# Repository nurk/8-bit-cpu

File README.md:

This repository contains my design of the Ben Eater 8-bit computer.  I call it an 8-CPU instead of a computer because to me it feels more like a CPU.

If you were to do a checkout of this, it is basically a KiCad project folder.  It will not contain all the symbols I used because the ones I designed I made global in KiCad, but I added a PDF of all the schematics.

You will also find my instruction set, the code to program the EEPROM's and the code to program the CPU which includes my test programs.

Below is a little badly written story of my journey.

## 8-bit CPU
I have always been intrigued by electronics by have never done anything with it.

A while back I found a video series by Ben Eater about building an 8-bit computer on breadboards ([YouTube](https://www.youtube.com/playlist?list=PLowKtXNTBypGqImE405J2565dvjafglHU)).  Watching the series I learned a lot about how CPU's (could) work and was really fascinated.  It all did not seem that complicated.

So after thinking about it for a while and checking my finances (It is not really cheap) I decided to build a variation of it.   But first I did some research and set some goals.

The research taught me that I should not skimp on breadboard quality.  There are a lot of people that write about this and the breadboards from BusBoard Prototype Systems seem to be one of the best.

Next I started digging into what types of 74 series logic chips there are.  I learned that the 74LS series that Ben uses are TTL logic chips but they are rather power hungry.  I decided I wanted to go with CMOS logic chips because they are more efficient.  In the end I went for 74HCT chips.  They are CMOS chips with TTL level support.  I went for this because I don't really know anything about this and I was not sure if I needed TTL level support in some parts.

So the chip series was decided and the breadboard brand was decided, now I needed a way to get all these things.  I started searching for those online and found the usual suspects: 
* Farnell
* Digikey
* Mouser
* ...

I live in Belgium so delivery costs, import taxes and VAT were important.  After a test order from [Mouser](https://www.mouser.be/) I learned that they take care of the VAT and the import taxes, and when you order over 50 EUR (excluding VAT) the delivery is free.  Just don't get caught at checkout because the prices on the site are without VAT.

I would also need a power supply.  I did not want to use a cut open USB cable but wanted some extra features.
* The device needed a global on/off switch
* I needed to be able to toggle the output on or off 
* Obviously the voltage should be settable
* The amperage should be limited
* I wanted over current protection so the output would be turned off if my creation would draw more than the set amps

On Amazon I found this [device](https://www.amazon.nl/dp/B0C1SMSW9F?ref=ppx_yo2ov_dt_b_product_details&th=1) that had all the features I wanted and it was not out of my budget.

Amazon was also used to buy the [wires](https://www.amazon.com.be/dp/B07V5FVSYL?psc=1&ref=ppx_yo2ov_dt_b_product_details) and initially some [resistors](https://www.amazon.com.be/dp/B0967TG6XR?ref=ppx_yo2ov_dt_b_product_details&th=1).  The wires were great and I ordered multiple of those because it seems this thing needs a lot of wire.  The resistors I hated and did not use.  The legs have a diameter of 0.3 mm which is just too thin.  When you want to insert them into a breadboard they just bend.  The resistors eventually also came from Mouser.

Next up, the goals of this build.
* I wanted a schematic of my build so I learned to use [KiCad](https://www.kicad.org/)
* Have more RAM so I could use all 8 address bits
* Have the RAM split so the first 128 bytes are for application memory and second 128 bytes are for data memory.  I did not want my application to overwrite itself
* Have an X register with +1 / -1 feature to enable specific loops and have it set the carry flag and zero flag
* Have a Stack
* Do not leave any input pins floating
* Have a 220 Ohm resistor on each LED (this includes each segment of the 7-segment display)
* Have a 100nF decoupling capacitor for each chip

The 220 Ohm resistor on each LED really made me think about component placement.  It dictated the layout on the breadboards.  Unlike what Ben does in his videos I could not just go from an output pin to ground.

After all the orders arrived I started building my CPU module by module in the order of the videos.  I would first design each module in KiCad and use my design to build it on breadboards.

While building I initially used 10k Ohm resistors to either pull-up or pull-down control signal pins.  That way I could use a jumper wire to switch its state without the pin being floating during the transition.  (The resistors were removed after wiring up the control signals.) The different modules were tested individually once they were finished.

When building the output module I noticed I did not order any 74HCT273 chips.  So I changed my design to use what I had which were 74HCT173 D-type flip flops.  In hindsight this seems to be a blessing in disguise because there seems to be a design issue with using the 74HCT273 as can be seen [here](https://www.youtube.com/playlist?list=PLyHdG0fm3K1j8sfvvdIarTFXVcFDdoBYp).

After finishing the clock, program counter, a register, alu, b register, output, ram and instruction register I decided to combine them and wire them up to the bus.  This is were I got hit with my first problem.

Whenever there were more than 4 LED's active in the RAM value and I would change the RAM output control signal (high to low or low to high) the RAM address register would reset.  I searched for hours what the cause could be but never figured it out.  I rewired stuff, replaced chips, disconnected modules from the bus, added pull-up and pull-down resisters, ... but everything stayed the same.  Motivation really sank so drastic measures needed to be taken.  Given the RAM address gets loaded by the program counter initially I decided I did not need a reset there and removed the reset line and tied the pins to ground.  *Problem solved*.

Next I built the last 4 modules: control logic, CPU flags, X register and stack.  When they were done I wired up everything.  Guess what, things did not work as expected.  Some of the problems I saw:
* The A register would reset randomly
* The X register would reset randomly
* The X register would load data from the bus at random points
* The X register would increment and decrement randomly
* The stack would increment and decrement randomly
* RAM not always writing

Those dreaded random resets were spreading.  Given I have no oscilloscope I could not really see what was going on with reset line but after some mental gymnastics I figured there must be some noise getting to the reset line.  Given I know nothing about electronics I started trying things.  

When I put a 10nF capacitor on the reset line close to the reset pin and ground of the A register it no longer did the random reset but the button to reset everything still worked.  I did the same with the X register and wired up the reset for the RAM address again with a 10nF capacitor.  No more random resets.  I still don't know why this is happening but it is fixed.  *Problem solved*.

Next up were the random actions in the X register and stack.  After searching the internet I found out that when you change the address on an EEPROM there is a period of time where the data is invalid (this is also in the datasheet).  This shows itself by data pins going high or low randomly during the invalid period.  This was triggering the random actions.

The first fix was not to trigger the load of the X register by just using an inverted control signal.  I used the non inverted control signal and the clock through a NAND gate to trigger the load.  This way the loading is tied to a clock transition which is in line with the rest of the design.  This made things better but did not solve everything.

After some more searching on the internet I found a post where someone explained that the entire computer reacts to the rising edge of the clock.  This includes the instruction register and the CPU flags which trigger address changes.  If you were to change the address on the falling edge of the clock the 'blips' on the EEPROM output would not matter.

I first thought about using the inverted clock for the instruction register and the CPU flags but decided against it.  I was not sure if this would have side effects.  Given I had some room below the instruction register I decided to add two more 74HCT173 D-type flip flops to latch the instruction register and the CPU flags on the falling edge of each clock.  These latched values are used as the address lines for the EEPROM's.  This solved all the problems of random actions occurring.

Lastly there was the problem of the RAM not always writing.  I was aware of issues with the RC circuit Ben has in his original design on the clock for the RAM input.  I already put in a diode to prevent back feeding any voltage as the capacitor discharges but I was still suspicious.  Given writing ram works with a push button in programming mode, which does not have an RC circuit on it, I figured it might work without.  After removing the RC circuit and just passing in the clock everything worked.

I now have an 8-bit breadboard CPU which supports addition, subtraction, push, pop, subroutines, ...

#### Some random bits:

I can program the CPU using the dip switches but that got old really quickly.  I wrote a little Arduino application that could program the CPU.  I just hook up the ground, the address lines, the data lines and write signal to the breadboard from an [Arduino Nano Every](https://store.arduino.cc/products/arduino-nano-every).  This saves a lot of time and does not discourage me from making changes and retesting.

On the internet there are many posts that say you have to add a lot of bulk capacitors to the breadboards in order to make it stable.  My CPU does not seem to need it.  It could be the quality of the breadboards, the fact that I used 74HCT chips or the quality of the power supply.  When running my Fibonacci program it draws a maximum of 350 mA.

I used an alternative to the EEPROM programmer designed by Ben.  Given I used an Arduino Nano Every, which has more digital pins, I did not have to combine the write signal into the shift registers.  I did have to rewire it because my EEPROM's did not seems to have the content I expected.

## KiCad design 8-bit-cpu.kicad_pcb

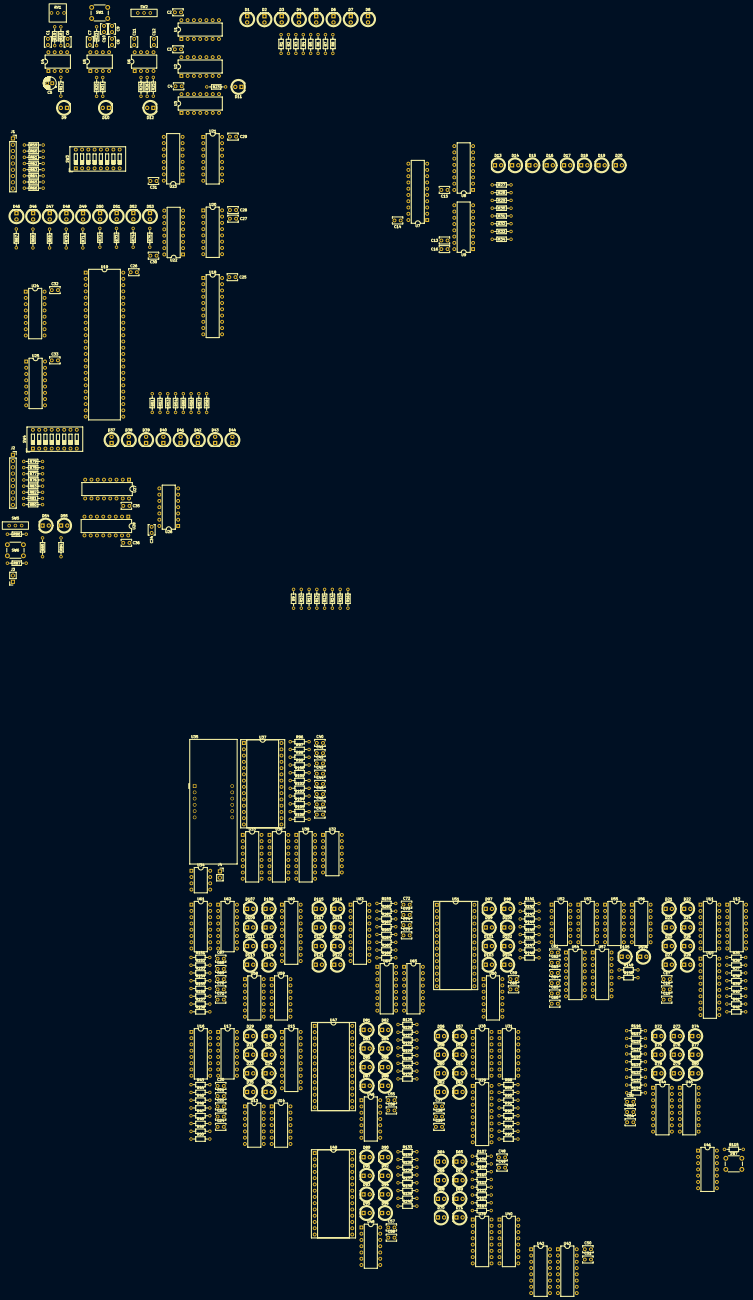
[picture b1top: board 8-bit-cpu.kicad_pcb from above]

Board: 2 copper layers, 440 parts (0 on the bottom side), 402 nets, no tracks yet.

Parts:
C1, C2, C3, C4, C7, C9, C10, C11, C14, C15, C16, C17, C18, C19, C20, C21, C22, C23, C24, C25, C26, C28, C29, C30, C31, C32, C33, C34, C35, C36, C37, C38, C39, C40, C41, C42, C45, C46, C47, C48, C49, C50, C51, C52, C53, C54, C55, C56, C57, C58, C59, C60, C61, C62, C63, C64, C65, C66, C67, C68, C69, C70, C71, C73, C74, C75: 100n; C_Disc_D4.0mm_W2.6mm_P2.50mm
C5: 1u; CP_Radial_D5.0mm_P2.00mm
C6, C8, C12, C13, C27, C43, C44, C72: 10n; C_Disc_D4.0mm_W2.6mm_P2.50mm
D1, D2, D3, D4, D5, D6, D7, D8, D13, D14, D15, D16, D17, D18, D19, D20, D21, D22, D23, D24, D25, D26, D27, D28, D29, D30, D31, D32, D33, D34, D35, D36, D37, D38, D39, D40, D41, D42, D43, D44, D55, D72, D73, D74, D107, D108, D109, D110, D111, D112, D113, D114: RED; LED_D5.0mm
D9, D10, D12, D45, D46, D47, D48, D49, D50, D51, D52, D53, D64, D65, D66, D67, D68, D69, D70, D71, D115, D116, D117, D118, D119, D120, D121, D122: YELLOW; LED_D5.0mm
D11, D81, D82, D83, D84, D85, D86, D87, D88, D89, D90, D91, D92, D93, D94, D95, D96, D97, D98, D99, D100, D101, D102, D103, D104: BLUE; LED_D5.0mm
D54, D56, D57, D58, D59, D60, D61, D62, D63, D75, D76, D77, D78, D79, D80, D105, D106: GREEN; LED_D5.0mm
J1: Arduino_Address_Programming_Header; PinSocket_1x09_P2.54mm_Vertical
J2: Arduino_Data_Programming_Header; PinSocket_1x09_P2.54mm_Vertical
J3: Arduino_Programming_Trigger_Header; PinSocket_1x02_P2.54mm_Vertical
J4: 2_Complement_Header; PinSocket_1x02_P2.54mm_Vertical
R1, R2, R3, R4, R5, R6, R7, R8, R17, R21, R23, R26, R27, R28, R29, R30, R31, R32, R33, R34, R35, R36, R37, R38, R39, R40, R41, R42, R43, R44, R45, R46, R47, R48, R49, R50, R51, R52, R53, R54, R55, R56, R57, R58, R67, R68, R69, R70, R71, R72, R73, R74, R75, R84, R85, R88, R89, R90, R91, R92, R93, R94, R95, R98, R99, R100, R101, R102, R103, R104, R105, R107, R108, R109, R110, R111, R112, R113, R114, R116, R117, R118, R119, R120, R121, R122, R123, R124, R125, R126, R127, R128, R129, R130, R131, R132, R133, R134, R135, R136, R137, R138, R139, R140, R141, R142, R143, R144, R145, R146, R147, R148, R149, R150, R151, R152, R153, R154, R155, R156, R157, R158, R159, R160, R161, R162, R163, R164, R165, R166: 220R; R_Axial_DIN0204_L3.6mm_D1.6mm_P7.62mm_Horizontal
R9, R10, R11, R12, R13, R14, R15, R16, R20, R24, R25, R59, R60, R61, R62, R63, R64, R65, R66, R76, R77, R78, R79, R80, R81, R82, R83, R86, R87, R106, R115: 10k; R_Axial_DIN0204_L3.6mm_D1.6mm_P7.62mm_Horizontal
R18, R19, R96: 1k; R_Axial_DIN0204_L3.6mm_D1.6mm_P7.62mm_Horizontal
R22: 1m; R_Axial_DIN0204_L3.6mm_D1.6mm_P7.62mm_Horizontal
R97: 100k; R_Axial_DIN0204_L3.6mm_D1.6mm_P7.62mm_Horizontal
RV1: 1m; Potentiometer_Bourns_3362U_Vertical
SW1, SW6, SW7: Button; SW_PUSH_6mm
SW2: Switch; Mini_Slide_Switch_CUI_THT_123
SW3, SW4: SW_DIP_x08; SW_DIP_SPSTx08_Slide_9.78x22.5mm_W7.62mm_P2.54mm
SW5: Programming Switch; Mini_Slide_Switch_CUI_THT_123
U1, U53, U55: 74HCT08; DIP-14_W7.62mm
U2, U46, U48, U50: 74HCT04; DIP-14_W7.62mm
U3: 74HCT32; DIP-14_W7.62mm
U4, U5, U6, U34: LMC555xN; DIP-8_W7.62mm
U7, U10, U15, U18, U29, U60, U63: 74HCT245; DIP-20_W7.62mm
U8, U9, U11, U12, U20, U21, U36, U38, U39, U40, U42, U43, U57: 74HCT173; DIP-16_W7.62mm
U13, U14: 74HCT86; DIP-14_W7.62mm
U16, U17: 74HCT283; DIP-16_W7.62mm
U19: 7130; DIP-48_W15.24mm
U22, U23, U24, U25, U27, U28, U54: 74HCT157; DIP-16_W7.62mm
U26, U41, U58, U59: 74HCT00; DIP-14_W7.62mm
U30, U31, U45: 74HCT161; DIP-16_W7.62mm
U32: 74HCT107; DIP-14_W7.62mm
U33: 74HCT139; DIP-16_W7.62mm
U35: LTC-5723HR; CA56-12SURKWA
U37, U47, U49, U51: AT28C64B; DIP-28_W15.24mm_Socket
U44: 74HCT138; DIP-16_W7.62mm
U52, U56: 74HCT02; DIP-14_W7.62mm
U61, U62, U64, U65: 74HCT193; DIP-16_W7.62mm

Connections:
+5V: C1.1, C2.1, C3.1, C4.1, C7.1, C11.1, C14.1, C15.1, C16.1, C17.1, C18.1, C19.1, C20.1, C21.1, C22.1, C23.1, C24.1, C25.1, C26.1, C28.1, C29.1, C30.1, C31.1, C32.1, C33.1, C34.1, C35.1, C36.1, C37.1, C38.1, C39.1, C42.1, C45.1, C46.1, C47.1, C48.1, C49.1, C50.1, C51.1, C52.1, C53.1, C54.1, C55.1, C56.1, C57.1, C58.1, C59.1, C60.1, C61.1, C62.1, C63.1, C64.1, C65.1, C66.1, C67.1, C68.1, C69.1, C70.1, C71.1, C73.1, C74.1, C75.1, J4.1, R18.1, R20.1, R22.1, R24.1, R25.1, R96.1, SW3.9, SW3.10, SW3.11, SW3.12, SW3.13, SW3.14, SW3.15, SW3.16, SW4.1, SW4.2, SW4.3, SW4.4, SW4.5, SW4.6, SW4.7, SW4.8, SW5.2 (B), SW6.1, SW7.1, U1.14 (VCC), U2.14 (VCC), U3.14 (VCC), U4.4 (R), U4.8 (VCC), U5.4 (R), U5.8 (VCC), U6.8 (VCC), U7.1 (DIR), U7.20 (VCC), U8.16 (VCC), U9.16 (VCC), U10.1 (DIR), U10.20 (VCC), U11.16 (VCC), U12.16 (VCC), U13.14 (VCC), U14.14 (VCC), U15.1 (DIR), U15.20 (VCC), U16.16 (VCC), U17.16 (VCC), U18.1 (DIR), U18.20 (VCC), U19.46 (R/~WR), U19.48 (VCC), U20.16 (VCC), U21.16 (VCC), U22.16 (VCC), U23.16 (VCC), U24.16 (VCC), U25.16 (VCC), U26.14 (VCC), U27.2 (1A), U27.16 (VCC), U28.16 (VCC), U29.20 (VCC), U30.16 (VCC), U31.16 (VCC), U32.1 (J), U32.4 (K), U32.8 (J), U32.10 (R), U32.11 (K), U32.13 (R), U34.4 (R), U34.8 (VCC), U36.16 (VCC), U37.27 (~WE), U37.28 (VCC), U38.16 (VCC), U39.16 (VCC), U40.16 (VCC), U41.14 (VCC), U42.16 (VCC), U43.16 (VCC), U44.6 (G1), U44.16 (VCC), U45.7 (PE), U45.9 (SPE), U45.10 (TE), U45.16 (VCC), U46.14 (VCC), U47.27 (~WE), U47.28 (VCC), U48.14 (VCC), U49.2 (A12), U49.27 (~WE), U49.28 (VCC), U50.14 (VCC), U51.23 (A11), U51.27 (~WE), U51.28 (VCC), U52.14 (VCC), U53.14 (VCC), U54.16 (VCC), U55.14 (VCC), U56.14 (VCC), U57.16 (VCC), U58.14 (VCC), U59.14 (VCC), U60.1 (DIR), U60.20 (VCC), U61.16 (VCC), U62.16 (VCC), U63.1 (DIR), U63.20 (VCC), U64.11 (~PL), U64.16 (VCC), U65.11 (~PL), U65.16 (VCC)
/A register/A_0: R34.1, U7.2 (A1), U9.3 (Q0), U17.5 (A0)
/A register/A_1: R33.1, U7.3 (A2), U9.4 (Q1), U17.3 (A1)
/A register/A_2: R32.1, U7.4 (A3), U9.5 (Q2), U17.14 (A2)
/A register/A_3: R31.1, U7.5 (A4), U9.6 (Q3), U17.12 (A3)
/A register/A_4: R30.1, U7.6 (A5), U8.3 (Q0), U16.5 (A0)
/A register/A_5: R29.1, U7.7 (A6), U8.4 (Q1), U16.3 (A1)
/A register/A_6: R28.1, U7.8 (A7), U8.5 (Q2), U16.14 (A2)
/A register/A_7: R27.1, U7.9 (A8), U8.6 (Q3), U16.12 (A3)
/A register/CLOCK: R23.1, U1.8, U2.5, U8.7 (CP), U9.7 (CP), U11.7 (CP), U12.7 (CP), U20.7 (CP), U21.7 (CP), U26.2, U30.2 (CP), U31.2 (CP), U36.7 (CP), U38.7 (CP), U57.7 (CP), U58.2, U58.4, U58.10, U58.12, U59.1
/A register/RESET: C13.1, C27.1, C72.1, U8.15 (MR), U9.15 (MR), U11.15 (MR), U12.15 (MR), U20.15 (MR), U21.15 (MR), U36.15 (MR), U38.15 (MR), U39.15 (MR), U40.15 (MR), U41.11, U42.15 (MR), U43.15 (MR), U57.15 (MR), U61.14 (MR), U62.14 (MR), U64.14 (MR), U65.14 (MR)
/A register/~A_INPUT: U8.9 (E1), U8.10 (E2), U9.9 (E1), U9.10 (E2), U46.12
/A register/~A_OUTPUT: U7.19 (OE), U48.2
/ALU/ALU_0: R50.1, U15.2 (A1), U17.4 (S0), U52.12
/ALU/ALU_1: R49.1, U15.3 (A2), U17.1 (S1), U52.11
/ALU/ALU_2: R48.1, U15.4 (A3), U17.13 (S2), U52.9
/ALU/ALU_3: R47.1, U15.5 (A4), U17.10 (S3), U52.8
/ALU/ALU_4: R46.1, U15.6 (A5), U16.4 (S0), U52.6
/ALU/ALU_5: R45.1, U15.7 (A6), U16.1 (S1), U52.5
/ALU/ALU_6: R44.1, U15.8 (A7), U16.13 (S2), U52.3
/ALU/ALU_7: R43.1, U15.9 (A8), U16.10 (S3), U52.2
/ALU/ALU_CARRY_OUT: U16.9 (C_{OUT}), U57.14 (D0)
/ALU/B_0: R42.1, U10.2 (A1), U12.3 (Q0), U14.1
/ALU/B_1: R41.1, U10.3 (A2), U12.4 (Q1), U14.4
/ALU/B_2: R40.1, U10.4 (A3), U12.5 (Q2), U14.9
/ALU/B_3: R39.1, U10.5 (A4), U12.6 (Q3), U14.12
/ALU/B_4: R38.1, U10.6 (A5), U11.3 (Q0), U13.1
/ALU/B_5: R37.1, U10.7 (A6), U11.4 (Q1), U13.4
/ALU/B_6: R36.1, U10.8 (A7), U11.5 (Q2), U13.9
/ALU/B_7: R35.1, U10.9 (A8), U11.6 (Q3), U13.12
/ALU/SUBTRACT: R140.1, U13.2, U13.5, U13.10, U13.13, U14.2, U14.5, U14.10, U14.13, U17.7 (C_{IN}), U49.19 (D7)
/ALU/~ALU_OUTPUT: U15.19 (OE), U48.4, U54.1 (~A/B)
/B register/~B_INPUT: U11.9 (E1), U11.10 (E2), U12.9 (E1), U12.10 (E2), U48.6
/B register/~B_OUTPUT: U10.19 (OE), U48.8
/BUS_0: R8.2, R16.1, U7.18 (B1), U9.14 (D0), U10.18 (B1), U12.14 (D0), U15.18 (B1), U18.18 (B1), U21.14 (D0), U25.2 (1A), U29.2 (A1), U31.3 (P0), U36.14 (D0), U40.14 (D0), U60.18 (B1), U62.15 (P0), U63.18 (B1)
/BUS_1: R7.2, R15.1, U7.17 (B2), U9.13 (D1), U10.17 (B2), U12.13 (D1), U15.17 (B2), U18.17 (B2), U21.13 (D1), U25.5 (2A), U29.3 (A2), U31.4 (P1), U36.13 (D1), U40.13 (D1), U60.17 (B2), U62.1, U63.17 (B2)
/BUS_2: R6.2, R14.1, U7.16 (B3), U9.12 (D2), U10.16 (B3), U12.12 (D2), U15.16 (B3), U18.16 (B3), U21.12 (D2), U25.11 (3A), U29.4 (A3), U31.5 (P2), U36.12 (D2), U40.12 (D2), U60.16 (B3), U62.10 (P2), U63.16 (B3)
/BUS_3: R5.2, R13.1, U7.15 (B4), U9.11 (D3), U10.15 (B4), U12.11 (D3), U15.15 (B4), U18.15 (B4), U21.11 (D3), U25.14 (4A), U29.5 (A4), U31.6 (P3), U36.11 (D3), U40.11 (D3), U60.15 (B4), U62.9 (P3), U63.15 (B4)
/BUS_4: R4.2, R12.1, U7.14 (B5), U8.14 (D0), U10.14 (B5), U11.14 (D0), U15.14 (B5), U18.14 (B5), U20.14 (D0), U24.2 (1A), U29.6 (A5), U30.3 (P0), U38.14 (D0), U39.14 (D0), U60.14 (B5), U61.15 (P0), U63.14 (B5)
/BUS_5: R3.2, R11.1, U7.13 (B6), U8.13 (D1), U10.13 (B6), U11.13 (D1), U15.13 (B6), U18.13 (B6), U20.13 (D1), U24.5 (2A), U29.7 (A6), U30.4 (P1), U38.13 (D1), U39.13 (D1), U60.13 (B6), U61.1, U63.13 (B6)
/BUS_6: R2.2, R10.1, U7.12 (B7), U8.12 (D2), U10.12 (B7), U11.12 (D2), U15.12 (B7), U18.12 (B7), U20.12 (D2), U24.11 (3A), U29.8 (A7), U30.5 (P2), U38.12 (D2), U39.12 (D2), U60.12 (B7), U61.10 (P2), U63.12 (B7)
/BUS_7: R1.2, R9.1, U7.11 (B8), U8.11 (D3), U10.11 (B8), U11.11 (D3), U15.11 (B8), U18.11 (B8), U20.11 (D3), U24.14 (4A), U29.9 (A8), U30.6 (P3), U38.11 (D3), U39.11 (D3), U60.11 (B8), U61.9 (P3), U63.11 (B8)
/CPU flags/ALU_ZERO: U53.8, U54.14 (4A)
/CPU flags/CARRY_FLAG: D106.2 (A), U42.12 (D2), U57.3 (Q0)
/CPU flags/X_0: R158.1, U56.2, U60.2 (A1), U62.3 (Q0)
/CPU flags/X_1: R157.1, U56.3, U60.3 (A2), U62.2 (Q1)
/CPU flags/X_2: R156.1, U56.5, U60.4 (A3), U62.6 (Q2)
/CPU flags/X_3: R155.1, U56.6, U60.5 (A4), U62.7 (Q3)
/CPU flags/X_4: R154.1, U56.8, U60.6 (A5), U61.3 (Q0)
/CPU flags/X_5: R153.1, U56.9, U60.7 (A6), U61.2 (Q1)
/CPU flags/X_6: R152.1, U56.11, U60.8 (A7), U61.6 (Q2)
/CPU flags/X_7: R151.1, U56.12, U60.9 (A8), U61.7 (Q3)
/CPU flags/X_ZERO: U54.13 (4B), U55.8
/CPU flags/ZERO_FLAG: D105.2 (A), U42.11 (D3), U57.4 (Q1)
/CPU flags/~FLAGS_INPUT: U48.12, U57.9 (E1), U57.10 (E2)
/Clock/ASTABLE_CLOCK: U1.3, U3.1
/Clock/ASTABLE_OUTPUT: R17.1, U1.1, U4.3 (Q)
/Clock/BISTABLE_OUTPUT: R26.1, U1.2, U2.3, U6.3 (Q)
/Clock/HALT: R139.1, U2.1, U49.18 (D6)
/Clock/MONOSTABLE_CLOCK: U1.6, U3.2
/Clock/MONOSTABLE_OUTPUT: R21.1, U1.4, U5.3 (Q)
/Clock/SELECTED_CLOCK: U1.9, U3.3
/Clock/~BISTABLE_OUTPUT: U1.5, U2.4
/Clock/~CLOCK: U2.6, U39.7 (CP), U40.7 (CP), U42.7 (CP), U43.7 (CP), U45.2 (CP)
/Clock/~HALT: U1.10, U2.2
/Control logic/COUNT_ENABLE: R132.1, U30.7 (PE), U31.7 (PE), U31.10 (TE), U47.19 (D7)
/Control logic/DEC: R147.1, U51.18 (D6), U58.5
/Control logic/EEPROM address buffer/EEPROM_3: U43.3 (Q0), U47.7 (A3), U49.7 (A3), U51.7 (A3)
/Control logic/EEPROM address buffer/EEPROM_4: U43.4 (Q1), U47.6 (A4), U49.6 (A4), U51.6 (A4)
/Control logic/EEPROM address buffer/EEPROM_5: U43.5 (Q2), U47.5 (A5), U49.5 (A5), U51.5 (A5)
/Control logic/EEPROM address buffer/EEPROM_6: U43.6 (Q3), U47.4 (A6), U49.4 (A6), U51.4 (A6)
/Control logic/EEPROM address buffer/EEPROM_7: U42.3 (Q0), U47.3 (A7), U49.3 (A7), U51.3 (A7)
/Control logic/EEPROM address buffer/EEPROM_8: U42.4 (Q1), U47.25 (A8), U49.25 (A8), U51.25 (A8)
/Control logic/EEPROM address buffer/EEPROM_9: U42.5 (Q2), U47.24 (A9), U49.24 (A9), U51.24 (A9)
/Control logic/EEPROM address buffer/EEPROM_10: U42.6 (Q3), U47.21 (A10), U49.21 (A10), U51.21 (A10)
/Control logic/INC: R148.1, U51.19 (D7), U58.1
/Control logic/INSTRUCTION_0: R114.1, U40.3 (Q0), U43.14 (D0)
/Control logic/INSTRUCTION_1: R113.1, U40.4 (Q1), U43.13 (D1)
/Control logic/INSTRUCTION_2: R112.1, U40.5 (Q2), U43.12 (D2)
/Control logic/INSTRUCTION_3: R111.1, U40.6 (Q3), U43.11 (D3)
/Control logic/INSTRUCTION_4: R110.1, U39.3 (Q0), U42.14 (D0)
/Control logic/INSTRUCTION_5: R109.1, U39.4 (Q1), U42.13 (D1)
/Control logic/Left Microcode EEPROM/MS_0: D74.2 (A), U44.1 (A), U45.14 (Q0), U47.10 (A0), U49.10 (A0), U51.10 (A0)
/Control logic/Left Microcode EEPROM/MS_1: D73.2 (A), U44.2 (B), U45.13 (Q1), U47.9 (A1), U49.9 (A1), U51.9 (A1)
/Control logic/Left Microcode EEPROM/MS_2: D72.2 (A), U44.3 (C), U45.12 (Q2), U47.8 (A2), U49.8 (A2), U51.8 (A2)
/Control logic/POP_STACK: R145.1, U51.16 (D4), U58.13
/Control logic/PUSH_STACK: R146.1, U51.17 (D5), U58.9
/Control logic/RAM_INPUT: R131.1, U26.1, U26.13, U47.18 (D6)
/Control logic/STACK_ADDRESS: R144.1, U28.14 (4A), U50.5, U51.15 (D3)
/Control logic/X_INPUT: R142.1, U51.12 (D1), U59.2
/Control logic/~COUNTER_OUTPUT: U29.19 (OE), U46.10
/Control logic/~INSTRUCTION_INPUT: U39.9 (E1), U39.10 (E2), U40.9 (E1), U40.10 (E2), U46.6
/Control logic/~JUMP: U30.9 (SPE), U31.9 (SPE), U46.8
/Control logic/~OUTPUT_INPUT: U36.9 (E1), U36.10 (E2), U38.9 (E1), U38.10 (E2), U48.10
/Control logic/~RAM_ADDDRESS_INPUT: U20.9 (E1), U20.10 (E2), U21.9 (E1), U21.10 (E2), U46.2
/Control logic/~RAM_OUTPUT: U18.19 (OE), U46.4
/Control logic/~RESET: U30.1 (MR), U31.1 (MR), U41.1, U41.8, U41.12, U41.13
/Control logic/~STACK_ADDRESS: U26.12, U50.6
/Control logic/~STACK_OUTPUT: U50.8, U63.19 (OE)
/Control logic/~X_OUTPUT: U50.12, U60.19 (OE)
/Output/2_COMPLEMENT: J4.2, R106.1, U37.21 (A10)
/Output/A0: U32.2 (~Q), U32.9 (C), U33.2 (A), U37.25 (A8)
/Output/A1: U32.6 (~Q), U33.3 (B), U37.24 (A9)
/RAM/RAM address/ARB_RAM_ADDRESS_7: R68.1, U19.13 (A7L), U19.35 (A7R), U27.4 (1Y)
/RAM/RAM address/ARB_STACK_ADDRESS: R67.1, U19.14 (A8L), U19.34 (A8R), U28.12 (4Y)
/RAM/RAM address/PROGRAMMING_MODE: D55.2 (A), R86.1, SW5.1 (A), U22.1 (~A/B), U23.1 (~A/B), U24.1 (~A/B), U25.1 (~A/B), U28.1 (~A/B)
/RAM/RAM address/RAM_ADDRESS_0: R75.1, U19.6 (A0L), U19.42 (A0R), U23.4 (1Y)
/RAM/RAM address/RAM_ADDRESS_1: R74.1, U19.7 (A1L), U19.41 (A1R), U23.7 (2Y)
/RAM/RAM address/RAM_ADDRESS_2: R73.1, U19.8 (A2L), U19.40 (A2R), U23.9 (3Y)
/RAM/RAM address/RAM_ADDRESS_3: R72.1, U19.9 (A3L), U19.39 (A3R), U23.12 (4Y)
/RAM/RAM address/RAM_ADDRESS_4: R71.1, U19.10 (A4L), U19.38 (A4R), U22.4 (1Y)
/RAM/RAM address/RAM_ADDRESS_5: R70.1, U19.11 (A5L), U19.37 (A5R), U22.7 (2Y)
/RAM/RAM address/RAM_ADDRESS_6: R69.1, U19.12 (A6L), U19.36 (A6R), U22.9 (3Y)
/RAM/RAM address/RAM_ADDRESS_7: U22.12 (4Y), U27.3 (1B)
/RAM/RAM logic/~RAM_READ_ENABLE: U19.47 (~CER), U26.9, U26.10, U28.4 (1Y)
/RAM/RAM logic/~RAM_WRITE_ENABLE: U19.1 (~CEL), U26.8
/RAM/RAM write value/RAM_WRITE_VALUE_0: U19.16 (I/O0L), U25.4 (1Y)
/RAM/RAM write value/RAM_WRITE_VALUE_1: U19.17 (I/O1L), U25.7 (2Y)
/RAM/RAM write value/RAM_WRITE_VALUE_2: U19.18 (I/O2L), U25.9 (3Y)
/RAM/RAM write value/RAM_WRITE_VALUE_3: U19.19 (I/O3L), U25.12 (4Y)
/RAM/RAM write value/RAM_WRITE_VALUE_4: U19.20 (I/O4L), U24.4 (1Y)
/RAM/RAM write value/RAM_WRITE_VALUE_5: U19.21 (I/O5L), U24.7 (2Y)
/RAM/RAM write value/RAM_WRITE_VALUE_6: U19.22 (I/O6L), U24.9 (3Y)
/RAM/RAM write value/RAM_WRITE_VALUE_7: U19.23 (I/O7L), U24.12 (4Y)
/Stack/DEC_STACK: U58.11, U65.4 (CPD)
/Stack/INC_STACK: U58.8, U65.5 (CPU)
/X Register/DEC_X: U58.6, U62.4 (CPD)
/X Register/INC_X: U58.3, U62.5 (CPU)
/X Register/X_INPUT_TRG: U59.3, U61.11 (~PL), U62.11 (~PL)
GND: C1.2, C2.2, C3.2, C4.2, C5.2, C6.2, C7.2, C8.2, C9.2, C10.2, C11.2, C12.2, C13.2, C14.2, C15.2, C16.2, C17.2, C18.2, C19.2, C20.2, C21.2, C22.2, C23.2, C24.2, C25.2, C26.2, C27.2, C28.2, C29.2, C30.2, C31.2, C32.2, C33.2, C34.2, C35.2, C36.2, C37.2, C38.2, C39.2, C40.2, C41.2, C42.2, C43.2, C44.2, C45.2, C46.2, C47.2, C48.2, C49.2, C50.2, C51.2, C52.2, C53.2, C54.2, C55.2, C56.2, C57.2, C58.2, C59.2, C60.2, C61.2, C62.2, C63.2, C64.2, C65.2, C66.2, C67.2, C68.2, C69.2, C70.2, C71.2, C72.2, C73.2, C74.2, C75.2, D1.1 (K), D2.1 (K), D3.1 (K), D4.1 (K), D5.1 (K), D6.1 (K), D7.1 (K), D8.1 (K), D9.1 (K), D10.1 (K), D11.1 (K), D12.1 (K), D13.1 (K), D14.1 (K), D15.1 (K), D16.1 (K), D17.1 (K), D18.1 (K), D19.1 (K), D20.1 (K), D21.1 (K), D22.1 (K), D23.1 (K), D24.1 (K), D25.1 (K), D26.1 (K), D27.1 (K), D28.1 (K), D29.1 (K), D30.1 (K), D31.1 (K), D32.1 (K), D33.1 (K), D34.1 (K), D35.1 (K), D36.1 (K), D37.1 (K), D38.1 (K), D39.1 (K), D40.1 (K), D41.1 (K), D42.1 (K), D43.1 (K), D44.1 (K), D45.1 (K), D46.1 (K), D47.1 (K), D48.1 (K), D49.1 (K), D50.1 (K), D51.1 (K), D52.1 (K), D53.1 (K), D56.1 (K), D57.1 (K), D58.1 (K), D59.1 (K), D60.1 (K), D61.1 (K), D62.1 (K), D63.1 (K), D64.1 (K), D65.1 (K), D66.1 (K), D67.1 (K), D68.1 (K), D69.1 (K), D70.1 (K), D71.1 (K), D81.1 (K), D82.1 (K), D83.1 (K), D84.1 (K), D85.1 (K), D86.1 (K), D87.1 (K), D88.1 (K), D89.1 (K), D90.1 (K), D91.1 (K), D92.1 (K), D93.1 (K), D94.1 (K), D95.1 (K), D96.1 (K), D97.1 (K), D98.1 (K), D99.1 (K), D100.1 (K), D101.1 (K), D102.1 (K), D103.1 (K), D104.1 (K), D107.1 (K), D108.1 (K), D109.1 (K), D110.1 (K), D111.1 (K), D112.1 (K), D113.1 (K), D114.1 (K), D115.1 (K), D116.1 (K), D117.1 (K), D118.1 (K), D119.1 (K), D120.1 (K), D121.1 (K), D122.1 (K), J1.1, J2.1, J3.1, R9.2, R10.2, R11.2, R12.2, R13.2, R14.2, R15.2, R16.2, R59.2, R60.2, R61.2, R62.2, R63.2, R64.2, R65.2, R66.2, R76.2, R77.2, R78.2, R79.2, R80.2, R81.2, R82.2, R83.2, R84.2, R85.2, R86.2, R87.2, R106.2, R115.2, R116.1, R117.1, R118.1, R119.2, R120.2, R121.2, R122.2, R123.2, R124.2, R149.2, R150.2, SW1.1, SW2.2 (B), U1.7 (GND), U1.12, U1.13, U2.7 (GND), U2.9, U2.11, U2.13, U3.4, U3.5, U3.7 (GND), U3.9, U3.10, U3.12, U3.13, U4.1 (GND), U5.1 (GND), U6.1 (GND), U6.6 (THR), U6.7 (DIS), U7.10 (GND), U8.1 (OE1), U8.2 (OE2), U8.8 (GND), U9.1 (OE1), U9.2 (OE2), U9.8 (GND), U10.10 (GND), U11.1 (OE1), U11.2 (OE2), U11.8 (GND), U12.1 (OE1), U12.2 (OE2), U12.8 (GND), U13.7 (GND), U14.7 (GND), U15.10 (GND), U16.8 (GND), U17.8 (GND), U18.10 (GND), U19.2 (R/~WL), U19.5 (~OEL), U19.15 (A9L), U19.24 (GND), U19.33 (A9R), U19.43 (~OER), U20.1 (OE1), U20.2 (OE2), U20.8 (GND), U21.1 (OE1), U21.2 (OE2), U21.8 (GND), U22.8 (GND), U22.15 (G), U23.8 (GND), U23.15 (G), U24.8 (GND), U24.15 (G), U25.8 (GND), U25.15 (G), U26.7 (GND), U27.5 (2A), U27.6 (2B), U27.8 (GND), U27.10 (3B), U27.11 (3A), U27.13 (4B), U27.14 (4A), U27.15 (G), U28.5 (2A), U28.6 (2B), U28.8 (GND), U28.10 (3B), U28.11 (3A), U28.13 (4B), U28.15 (G), U29.1 (DIR), U29.10 (GND), U30.8 (GND), U31.8 (GND), U32.7 (GND), U33.1 (G), U33.8 (GND), U33.13 (B), U33.14 (A), U33.15 (G), U34.1 (GND), U36.1 (OE1), U36.2 (OE2), U36.8 (GND), U37.2 (A12), U37.14 (GND), U37.20 (~CS), U37.22 (~OE), U37.23 (A11), U38.1 (OE1), U38.2 (OE2), U38.8 (GND), U39.1 (OE1), U39.2 (OE2), U39.8 (GND), U40.1 (OE1), U40.2 (OE2), U40.8 (GND), U41.7 (GND), U42.1 (OE1), U42.2 (OE2), U42.8 (GND), U42.9 (E1), U42.10 (E2), U43.1 (OE1), U43.2 (OE2), U43.8 (GND), U43.9 (E1), U43.10 (E2), U44.4 (G2A), U44.5 (G2B), U44.8 (GND), U45.3 (P0), U45.4 (P1), U45.5 (P2), U45.6 (P3), U45.8 (GND), U46.7 (GND), U47.2 (A12), U47.14 (GND), U47.20 (~CS), U47.22 (~OE), U47.23 (A11), U48.7 (GND), U49.14 (GND), U49.20 (~CS), U49.22 (~OE), U49.23 (A11), U50.1, U50.3, U50.7 (GND), U50.11, U51.2 (A12), U51.14 (GND), U51.20 (~CS), U51.22 (~OE), U52.7 (GND), U53.7 (GND), U53.12, U53.13, U54.2 (1A), U54.3 (1B), U54.5 (2A), U54.6 (2B), U54.8 (GND), U54.10 (3B), U54.11 (3A), U54.15 (G), U55.7 (GND), U55.12, U55.13, U56.7 (GND), U57.1 (OE1), U57.2 (OE2), U57.8 (GND), U57.11 (D3), U57.12 (D2), U58.7 (GND), U59.4, U59.5, U59.7 (GND), U59.9, U59.10, U59.12, U59.13, U60.10 (GND), U61.8 (GND), U62.8 (GND), U63.10 (GND), U64.1, U64.8 (GND), U64.9 (P3), U64.10 (P2), U64.15 (P0), U65.1, U65.8 (GND), U65.9 (P3), U65.10 (P2), U65.15 (P0)
unnamed: D1.2 (A), R1.1
unnamed: D2.2 (A), R2.1
unnamed: D3.2 (A), R3.1
unnamed: D4.2 (A), R4.1
unnamed: D5.2 (A), R5.1
unnamed: D6.2 (A), R6.1
unnamed: D7.2 (A), R7.1
unnamed: D8.2 (A), R8.1
unnamed: D9.2 (A), R17.2
unnamed: D10.2 (A), R21.2
unnamed: D11.2 (A), R23.2
unnamed: D12.2 (A), R26.2
unnamed: D13.2 (A), R27.2
unnamed: D14.2 (A), R28.2
unnamed: D15.2 (A), R29.2
unnamed: D16.2 (A), R30.2
unnamed: D17.2 (A), R31.2
unnamed: D18.2 (A), R32.2
unnamed: D19.2 (A), R33.2
unnamed: D20.2 (A), R34.2
unnamed: D21.2 (A), R35.2
unnamed: D22.2 (A), R36.2
unnamed: D23.2 (A), R37.2
unnamed: D24.2 (A), R38.2
unnamed: D25.2 (A), R39.2
unnamed: D26.2 (A), R40.2
unnamed: D27.2 (A), R41.2
unnamed: D28.2 (A), R42.2
unnamed: D29.2 (A), R43.2
unnamed: D30.2 (A), R44.2
unnamed: D31.2 (A), R45.2
unnamed: D32.2 (A), R46.2
unnamed: D33.2 (A), R47.2
unnamed: D34.2 (A), R48.2
unnamed: D35.2 (A), R49.2
unnamed: D36.2 (A), R50.2
unnamed: D37.2 (A), R51.2
unnamed: D38.2 (A), R52.2
unnamed: D39.2 (A), R53.2
unnamed: D40.2 (A), R54.2
unnamed: D41.2 (A), R55.2
unnamed: D42.2 (A), R56.2
unnamed: D43.2 (A), R57.2
unnamed: D44.2 (A), R58.2
unnamed: D45.2 (A), R67.2
unnamed: D46.2 (A), R68.2
unnamed: D47.2 (A), R69.2
unnamed: D48.2 (A), R70.2
unnamed: D49.2 (A), R71.2
unnamed: D50.2 (A), R72.2
unnamed: D51.2 (A), R73.2
unnamed: D52.2 (A), R74.2
unnamed: D53.2 (A), R75.2
unnamed: D54.2 (A), SW5.3 (C)
unnamed: D54.1 (K), R85.1
unnamed: D55.1 (K), R84.1
unnamed: D56.2 (A), R88.2
unnamed: D57.2 (A), R89.2
unnamed: D58.2 (A), R90.2
unnamed: D59.2 (A), R91.2
unnamed: D60.2 (A), R92.2
unnamed: D61.2 (A), R93.2
unnamed: D62.2 (A), R94.2
unnamed: D63.2 (A), R95.2
unnamed: D64.2 (A), R107.2
unnamed: D65.2 (A), R108.2
unnamed: D66.2 (A), R109.2
unnamed: D67.2 (A), R110.2
unnamed: D68.2 (A), R111.2
unnamed: D69.2 (A), R112.2
unnamed: D70.2 (A), R113.2
unnamed: D71.2 (A), R114.2
unnamed: D72.1 (K), R116.2
unnamed: D73.1 (K), R117.2
unnamed: D74.1 (K), R118.2
unnamed: D75.2 (A), U44.10 (Y5)
unnamed: D75.1 (K), R119.1
unnamed: D76.2 (A), U44.11 (Y4)
unnamed: D76.1 (K), R120.1
unnamed: D77.2 (A), U44.12 (Y3)
unnamed: D77.1 (K), R121.1
unnamed: D78.2 (A), U44.13 (Y2)
unnamed: D78.1 (K), R122.1
unnamed: D79.2 (A), U44.14 (Y1)
unnamed: D79.1 (K), R123.1
unnamed: D80.2 (A), U44.15 (Y0)
unnamed: D80.1 (K), R124.1
unnamed: D81.2 (A), R125.2
unnamed: D82.2 (A), R126.2
unnamed: D83.2 (A), R127.2
unnamed: D84.2 (A), R128.2
unnamed: D85.2 (A), R129.2
unnamed: D86.2 (A), R130.2
unnamed: D87.2 (A), R131.2
unnamed: D88.2 (A), R132.2
unnamed: D89.2 (A), R133.2
unnamed: D90.2 (A), R134.2
unnamed: D91.2 (A), R135.2
unnamed: D92.2 (A), R136.2
unnamed: D93.2 (A), R137.2
unnamed: D94.2 (A), R138.2
unnamed: D95.2 (A), R139.2
unnamed: D96.2 (A), R140.2
unnamed: D97.2 (A), R141.2
unnamed: D98.2 (A), R142.2
unnamed: D99.2 (A), R143.2
unnamed: D100.2 (A), R144.2
unnamed: D101.2 (A), R145.2
unnamed: D102.2 (A), R146.2
unnamed: D103.2 (A), R147.2
unnamed: D104.2 (A), R148.2
unnamed: D105.1 (K), R149.1
unnamed: D106.1 (K), R150.1
unnamed: D107.2 (A), R151.2
unnamed: D108.2 (A), R152.2
unnamed: D109.2 (A), R153.2
unnamed: D110.2 (A), R154.2
unnamed: D111.2 (A), R155.2
unnamed: D112.2 (A), R156.2
unnamed: D113.2 (A), R157.2
unnamed: D114.2 (A), R158.2
unnamed: D115.2 (A), R159.2
unnamed: D116.2 (A), R160.2
unnamed: D117.2 (A), R161.2
unnamed: D118.2 (A), R162.2
unnamed: D119.2 (A), R163.2
unnamed: D120.2 (A), R164.2
unnamed: D121.2 (A), R165.2
unnamed: D122.2 (A), R166.2
unnamed: J1.2, R59.1, SW3.1, U22.13 (4B)
unnamed: J1.3, R60.1, SW3.2, U22.10 (3B)
unnamed: J1.4, R61.1, SW3.3, U22.6 (2B)
unnamed: J1.5, R62.1, SW3.4, U22.3 (1B)
unnamed: J1.6, R63.1, SW3.5, U23.13 (4B)
unnamed: J1.7, R64.1, SW3.6, U23.10 (3B)
unnamed: J1.8, R65.1, SW3.7, U23.6 (2B)
unnamed: J1.9, R66.1, SW3.8, U23.3 (1B)
unnamed: J2.2, R79.1, SW4.16, U24.13 (4B)
unnamed: J2.3, R78.1, SW4.15, U24.10 (3B)
unnamed: J2.4, R77.1, SW4.14, U24.6 (2B)
unnamed: J2.5, R76.1, SW4.13, U24.3 (1B)
unnamed: J2.6, R83.1, SW4.12, U25.13 (4B)
unnamed: J2.7, R82.1, SW4.11, U25.10 (3B)
unnamed: J2.8, R81.1, SW4.10, U25.6 (2B)
unnamed: J2.9, R80.1, SW4.9, U25.3 (1B)
unnamed: J3.2, R87.1, SW6.2, U28.3 (1B)
unnamed: R19.2, RV1.3
unnamed: R115.1, SW7.2, U41.9, U41.10
unnamed: R24.2, SW2.1 (A), U6.2 (TR)
unnamed: R25.2, SW2.3 (C), U6.4 (R)
unnamed: C6.1, U4.5 (CV)
unnamed: R18.2, R19.1, U4.7 (DIS)
unnamed: C5.1, RV1.2, U4.2 (TR), U4.6 (THR)
unnamed: C8.1, U5.5 (CV)
unnamed: C9.1, C10.1, R22.2, U5.6 (THR), U5.7 (DIS)
unnamed: R20.2, SW1.2, U5.2 (TR)
unnamed: C12.1, U6.5 (CV)
unnamed: U13.3, U16.6 (B0)
unnamed: U13.6, U16.2 (B1)
unnamed: U13.8, U16.15 (B2)
unnamed: U13.11, U16.11 (B3)
unnamed: U16.7 (C_{IN}), U17.9 (C_{OUT})
unnamed: U14.3, U17.6 (B0)
unnamed: U14.6, U17.2 (B1)
unnamed: U14.8, U17.15 (B2)
unnamed: U14.11, U17.11 (B3)
unnamed: R58.1, U18.2 (A1), U19.32 (I/O0R)
unnamed: R57.1, U18.3 (A2), U19.31 (I/O1R)
unnamed: R56.1, U18.4 (A3), U19.30 (I/O2R)
unnamed: R55.1, U18.5 (A4), U19.29 (I/O3R)
unnamed: R54.1, U18.6 (A5), U19.28 (I/O4R)
unnamed: R53.1, U18.7 (A6), U19.27 (I/O5R)
unnamed: R52.1, U18.8 (A7), U19.26 (I/O6R)
unnamed: R51.1, U18.9 (A8), U19.25 (I/O7R)
unnamed: U20.3 (Q0), U22.2 (1A)
unnamed: U20.4 (Q1), U22.5 (2A)
unnamed: U20.5 (Q2), U22.11 (3A)
unnamed: U20.6 (Q3), U22.14 (4A)
unnamed: U21.3 (Q0), U23.2 (1A)
unnamed: U21.4 (Q1), U23.5 (2A)
unnamed: U21.5 (Q2), U23.11 (3A)
unnamed: U21.6 (Q3), U23.14 (4A)
unnamed: U26.3, U26.4, U26.5
unnamed: U26.11, U27.1 (~A/B)
unnamed: U26.6, U28.2 (1A)
unnamed: R95.1, U29.18 (B1), U31.14 (Q0)
unnamed: R94.1, U29.17 (B2), U31.13 (Q1)
unnamed: R93.1, U29.16 (B3), U31.12 (Q2)
unnamed: R92.1, U29.15 (B4), U31.11 (Q3)
unnamed: R91.1, U29.14 (B5), U30.14 (Q0)
unnamed: R90.1, U29.13 (B6), U30.13 (Q1)
unnamed: R89.1, U29.12 (B7), U30.12 (Q2)
unnamed: R88.1, U29.11 (B8), U30.11 (Q3)
unnamed: U30.10 (TE), U31.15 (TC)
unnamed: U32.12 (C), U34.3 (Q)
unnamed: C40.1, U32.14 (VCC)
unnamed: U33.4 (Y0), U35.6 (CC4)
unnamed: U33.5 (Y1), U35.8 (CC3)
unnamed: U33.6 (Y2), U35.9 (CC2)
unnamed: U33.7 (Y3), U35.12 (CC1)
unnamed: C41.1, U33.16 (VCC)
unnamed: C44.1, U34.5 (CV)
unnamed: R96.2, R97.1, U34.7 (DIS)
unnamed: C43.1, R97.2, U34.2 (TR), U34.6 (THR)
unnamed: R105.1, U35.3 (DPX)
unnamed: R104.1, U35.11 (a)
unnamed: R103.1, U35.7 (b)
unnamed: R102.1, U35.4 (c)
unnamed: R101.1, U35.2 (d)
unnamed: R100.1, U35.1 (e)
unnamed: R99.1, U35.10 (f)
unnamed: R98.1, U35.5 (g)
unnamed: U36.3 (Q0), U37.10 (A0)
unnamed: U36.4 (Q1), U37.9 (A1)
unnamed: U36.5 (Q2), U37.8 (A2)
unnamed: U36.6 (Q3), U37.7 (A3)
unnamed: U37.6 (A4), U38.3 (Q0)
unnamed: U37.5 (A5), U38.4 (Q1)
unnamed: U37.4 (A6), U38.5 (Q2)
unnamed: U37.3 (A7), U38.6 (Q3)
unnamed: R98.2, U37.11 (D0)
unnamed: R99.2, U37.12 (D1)
unnamed: R100.2, U37.13 (D2)
unnamed: R101.2, U37.15 (D3)
unnamed: R102.2, U37.16 (D4)
unnamed: R103.2, U37.17 (D5)
unnamed: R104.2, U37.18 (D6)
unnamed: R105.2, U37.19 (D7)
unnamed: R108.1, U39.5 (Q2)
unnamed: R107.1, U39.6 (Q3)
unnamed: U41.3, U41.4, U41.5
unnamed: U41.2, U44.9 (Y6)
unnamed: U41.6, U45.1 (MR)
unnamed: R125.1, U46.13, U47.11 (D0)
unnamed: R126.1, U46.11, U47.12 (D1)
unnamed: R127.1, U46.9, U47.13 (D2)
unnamed: R128.1, U46.5, U47.15 (D3)
unnamed: R129.1, U46.3, U47.16 (D4)
unnamed: R130.1, U46.1, U47.17 (D5)
unnamed: R133.1, U48.13, U49.11 (D0)
unnamed: R134.1, U48.11, U49.12 (D1)
unnamed: R135.1, U48.9, U49.13 (D2)
unnamed: R136.1, U48.5, U49.15 (D3)
unnamed: R137.1, U48.3, U49.16 (D4)
unnamed: R138.1, U48.1, U49.17 (D5)
unnamed: R141.1, U50.13, U51.11 (D0)
unnamed: R143.1, U50.9, U51.13 (D2)
unnamed: U52.1, U53.1
unnamed: U52.4, U53.2
unnamed: U52.10, U53.4
unnamed: U52.13, U53.5
unnamed: U53.3, U53.9
unnamed: U53.6, U53.10
unnamed: U54.12 (4Y), U57.13 (D1)
unnamed: U55.1, U56.1
unnamed: U55.2, U56.4
unnamed: U55.3, U55.9
unnamed: U55.4, U56.10
unnamed: U55.5, U56.13
unnamed: U55.6, U55.10
unnamed: U61.4 (CPD), U62.13 (TCD)
unnamed: U61.5 (CPU), U62.12 (TCU)
unnamed: R166.1, U63.2 (A1), U65.3 (Q0)
unnamed: R165.1, U63.3 (A2), U65.2 (Q1)
unnamed: R164.1, U63.4 (A3), U65.6 (Q2)
unnamed: R163.1, U63.5 (A4), U65.7 (Q3)
unnamed: R162.1, U63.6 (A5), U64.3 (Q0)
unnamed: R161.1, U63.7 (A6), U64.2 (Q1)
unnamed: R160.1, U63.8 (A7), U64.6 (Q2)
unnamed: R159.1, U63.9 (A8), U64.7 (Q3)
unnamed: U64.4 (CPD), U65.13 (TCD)
unnamed: U64.5 (CPU), U65.12 (TCU)

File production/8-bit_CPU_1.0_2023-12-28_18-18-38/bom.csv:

Designator,Footprint,Quantity,Value,LCSC Part #
"C1, C10, C11, C14, C15, C16, C18, C19, C2, C20, C21, C22, C23, C24, C25, C26, C27, C29, C3, C30, C31, C32, C33, C34, C35, C36, C37, C39, C4, C40, C41, C42, C43, C44, C47, C48, C49, C52, C53, C55, C56, C57, C58, C59, C60, C61, C62, C63, C64, C65, C66, C67, C68, C7, C70, C71, C72, C73, C74, C76, C77, C78, C80, C81, C82, C9",C_Disc_D4.0mm_W2.6mm_P2.50mm,66,100n,
"C12, C45, C46, C6, C8",C_Disc_D4.0mm_W2.6mm_P2.50mm,5,10n,
"C13, C17, C28, C38, C50, C51, C54, C69, C75, C79",C_Disc_D4.0mm_W2.6mm_P2.50mm,10,10n,DNP
C5,CP_Radial_D5.0mm_P2.00mm,1,1u,
"D1, D107, D108, D109, D110, D111, D112, D113, D114, D13, D14, D15, D16, D17, D18, D19, D2, D20, D21, D22, D23, D24, D25, D26, D27, D28, D29, D3, D30, D31, D32, D33, D34, D35, D36, D37, D38, D39, D4, D40, D41, D42, D43, D44, D5, D55, D6, D7, D72, D73, D74, D8",LED_D5.0mm,52,RED,
"D10, D115, D116, D117, D118, D119, D12, D120, D121, D122, D45, D46, D47, D48, D49, D50, D51, D52, D53, D64, D65, D66, D67, D68, D69, D70, D71, D9",LED_D5.0mm,28,YELLOW,
"D100, D101, D102, D103, D104, D11, D81, D82, D83, D84, D85, D86, D87, D88, D89, D90, D91, D92, D93, D94, D95, D96, D97, D98, D99",LED_D5.0mm,25,BLUE,
"D105, D106, D54, D56, D57, D58, D59, D60, D61, D62, D63, D75, D76, D77, D78, D79, D80",LED_D5.0mm,17,GREEN,
J1,PinSocket_1x09_P2.54mm_Vertical,1,Arduino_Address_Programming_Header,
J2,PinSocket_1x09_P2.54mm_Vertical,1,Arduino_Data_Programming_Header,
J3,PinSocket_1x02_P2.54mm_Vertical,1,Arduino_Programming_Trigger_Header,
J4,PinSocket_1x02_P2.54mm_Vertical,1,2_Complement_Header,
"R1, R100, R101, R102, R103, R104, R105, R107, R108, R109, R110, R111, R112, R113, R114, R116, R117, R118, R119, R120, R121, R122, R123, R124, R125, R126, R127, R128, R129, R130, R131, R132, R133, R134, R135, R136, R137, R138, R139, R140, R141, R142, R143, R144, R145, R146, R147, R148, R149, R150, R151, R152, R153, R154, R155, R156, R157, R158, R159, R160, R161, R162, R163, R164, R165, R166, R17, R2, R21, R23, R26, R27, R28, R29, R3, R30, R31, R32, R33, R34, R35, R36, R37, R38, R39, R4, R40, R41, R42, R43, R44, R45, R46, R47, R48, R49, R5, R50, R51, R52, R53, R54, R55, R56, R57, R58, R6, R67, R68, R69, R7, R70, R71, R72, R73, R74, R75, R8, R84, R85, R88, R89, R90, R91, R92, R93, R94, R95, R98, R99",R_Axial_DIN0204_L3.6mm_D1.6mm_P7.62mm_Horizontal,130,220R,
"R10, R106, R11, R115, R12, R13, R14, R15, R16, R20, R24, R25, R59, R60, R61, R62, R63, R64, R65, R66, R76, R77, R78, R79, R80, R81, R82, R83, R86, R87, R9",R_Axial_DIN0204_L3.6mm_D1.6mm_P7.62mm_Horizontal,31,10k,
"R18, R19, R96",R_Axial_DIN0204_L3.6mm_D1.6mm_P7.62mm_Horizontal,3,1k,
R22,R_Axial_DIN0204_L3.6mm_D1.6mm_P7.62mm_Horizontal,1,1m,
R97,R_Axial_DIN0204_L3.6mm_D1.6mm_P7.62mm_Horizontal,1,100k,
RV1,Potentiometer_Bourns_3362U_Vertical,1,1m,
"SW1, SW6, SW7",SW_PUSH_6mm,3,Button,
SW2,Mini_Slide_Switch_CUI_THT_123,1,Switch,
"SW3, SW4",SW_DIP_SPSTx08_Slide_9.78x22.5mm_W7.62mm_P2.54mm,2,SW_DIP_x08,
SW5,Mini_Slide_Switch_CUI_THT_123,1,Programming Switch,
"U1, U53, U55",DIP-14_W7.62mm,3,74HCT08,
"U10, U15, U18, U29, U60, U63, U7",DIP-20_W7.62mm,7,74HCT245,
"U11, U12, U20, U21, U36, U38, U39, U40, U42, U43, U57, U8, U9",DIP-16_W7.62mm,13,74HCT173,
"U13, U14",DIP-14_W7.62mm,2,74HCT86,
"U16, U17",DIP-16_W7.62mm,2,74HCT283,
U19,DIP-48_W15.24mm,1,7130,
"U2, U46, U48, U50",DIP-14_W7.62mm,4,74HCT04,
"U22, U23, U24, U25, U27, U28, U54",DIP-16_W7.62mm,7,74HCT157,
"U26, U41, U58, U59",DIP-14_W7.62mm,4,74HCT00,
U3,DIP-14_W7.62mm,1,74HCT32,
"U30, U31, U45",DIP-16_W7.62mm,3,74HCT161,
U32,DIP-14_W7.62mm,1,74HCT107,
U33,DIP-16_W7.62mm,1,74HCT139,
"U34, U4, U5, U6",DIP-8_W7.62mm,4,LMC555xN,
U35,CA56-12SURKWA,1,LTC-5723HR,
"U37, U47, U49, U51",DIP-28_W15.24mm_Socket,4,AT28C64B,
U44,DIP-16_W7.62mm,1,74HCT138,
"U52, U56",DIP-14_W7.62mm,2,74HCT02,
"U61, U62, U64, U65",DIP-16_W7.62mm,4,74HCT193,

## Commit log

2023-12-10 init
2023-12-10 ram address 7 led now uses the arbitrated signal
2023-12-11 finished the control logic
2023-12-11 redid the eeprom
2023-12-12 add pdf for instructions
2023-12-13 some rerouting
2023-12-13 fixed gate type in cpu flags
2023-12-15 added code to program eeproms
2023-12-16 Fixed out instructions, no CE. Added note about RESET line in RaI
2023-12-16 added stack and x register. Added logic for stack_address so ram address 7 gets passes and ram address 8 is high
2023-12-17 changed symbols
2023-12-17 updated instruction set
2023-12-17 updated microcode programmer
2023-12-17 I have no clue what I did
2023-12-17 some cleanup
2023-12-18 added arduino code to program the cpu
2023-12-18 add arduino headers for programming
2023-12-18 first attempt at fibonacci
2023-12-18 cleanup
2023-12-20 trying to solve issues
2023-12-21 it kinda works
2023-12-21 fixed push address, push pop tested, fibonacci loops correctly
2023-12-22 fixed RTS
2023-12-22 added breadboard layout
2023-12-22 readme
2023-12-22 regenerated BOM
2023-12-27 some silly extra code to use the x register and the stack
2023-12-27 rollback
2023-12-27 cannot do incx before JC because this also sets the cpu flags
2023-12-28 alu carry out goes through selector now so we do not set the carry flag when we do incx or decx
2023-12-28 some more layout
2023-12-28 git ignore
2023-12-29 used an auto router
2023-12-29 replot
2023-12-30 routing
2023-12-30 kicad update
